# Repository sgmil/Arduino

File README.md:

# Useful Arduino templates and files
### Scripts folder contains bash scripts for accessing arduino-cli from geany
### ESPOTA.py for OTA uploads of .bin file on ESP8266
### Arduino templates/files/  contains arduino .ino and .geany files for geany

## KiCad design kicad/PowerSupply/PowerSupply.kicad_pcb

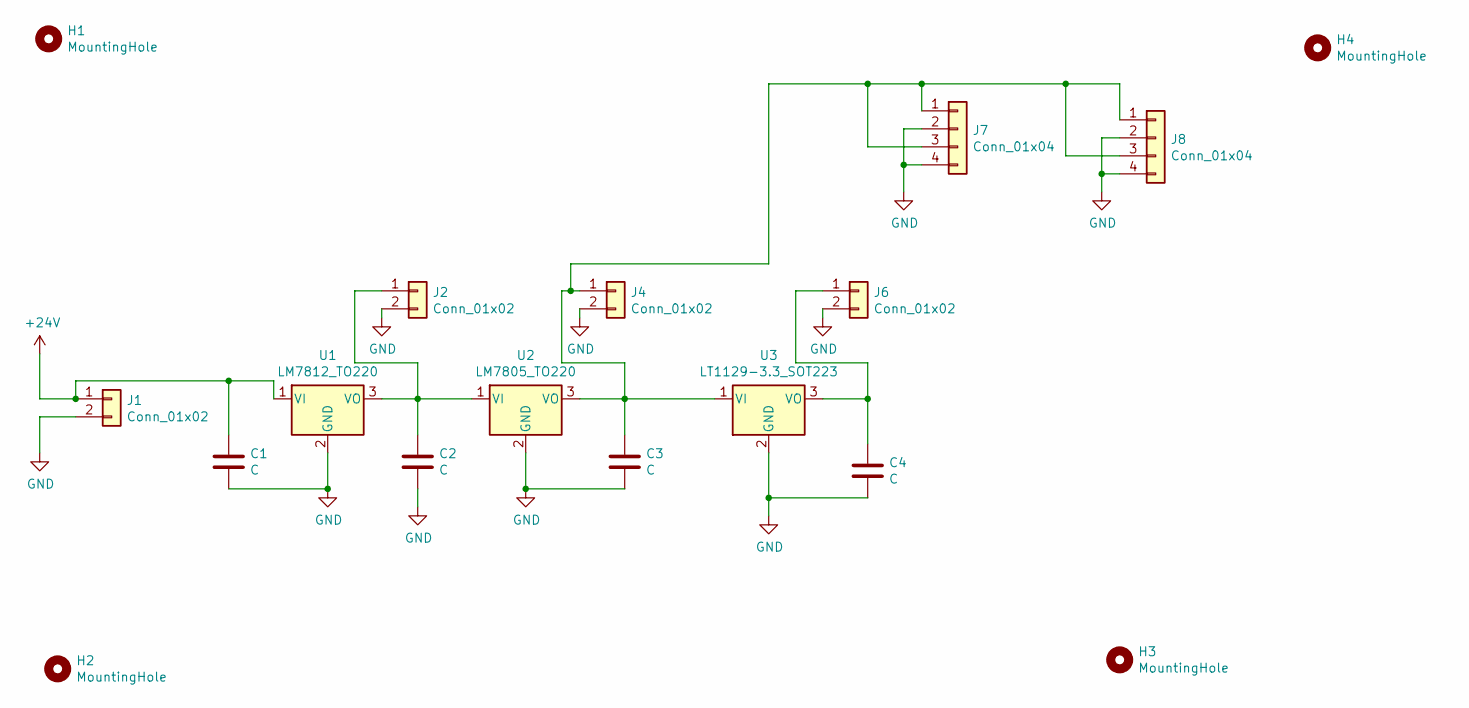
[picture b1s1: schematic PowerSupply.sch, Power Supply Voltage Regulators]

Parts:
C1, C2, C3, C4: C; CP_Radial_D5.0mm_P2.50mm
H1, H2, H3, H4: MountingHole; MountingHole_2.5mm
J1, J2, J4, J6: Conn_01x02; PINHEAD1-2
J7, J8: Conn_01x04; Pin_Header_Straight_1x04_Pitch2.54mm
U1: LM7812_TO220; TO-220-3_Vertical
U2: LM7805_TO220; TO-220-3_Vertical
U3: LT1129-3.3_SOT223; TO-220-3_Vertical

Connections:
+24V: C1.1, J1.1, U1.1 (VI)
GND: C1.2, C2.2, C3.2, C4.2, J1.2, J2.2, J4.2, J6.2, J7.2, J7.4, J8.2, J8.4, U1.2 (GND), U2.2 (GND), U3.2 (GND)
unnamed: C2.1, J2.1, U1.3 (VO), U2.1 (VI)
unnamed: C3.1, J4.1, J7.1, J7.3, J8.1, J8.3, U2.3 (VO), U3.1 (VI)
unnamed: C4.1, J6.1, U3.3 (VO)

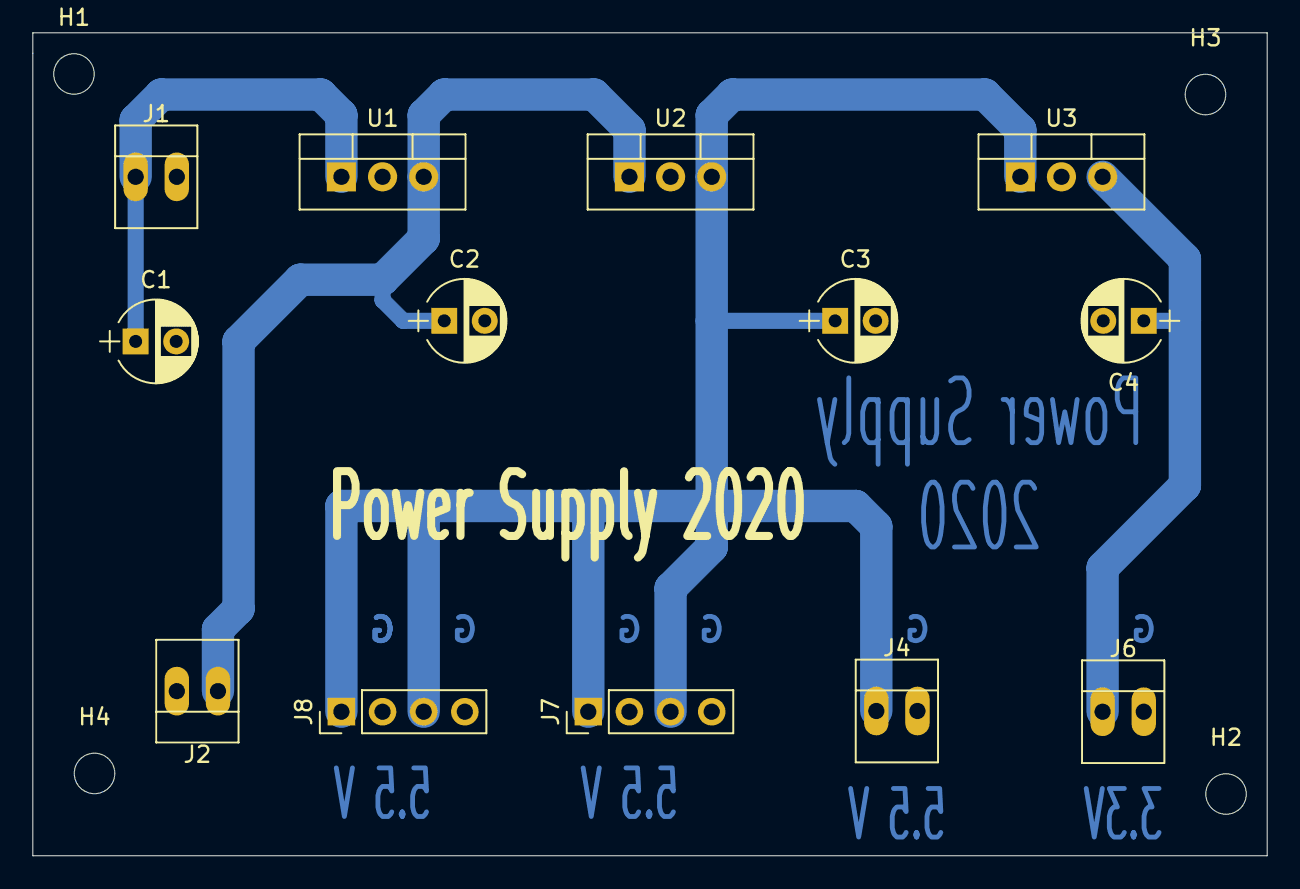
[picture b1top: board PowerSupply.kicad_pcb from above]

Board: 2 copper layers, 76.2 x 50.8 mm, 17 parts (0 on the bottom side), 5 nets.

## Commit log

2020-01-02 add extra line to top of template and adjust
2020-01-02 templates added
2020-01-03 change to sed to remove #define
2020-01-04 using #define headers
2020-01-04 modified templates for #define header
2020-01-05 header changes
2020-01-05 redo links
2020-01-05 add to setup and main
2020-01-06 clean up appearance, add documentation
2020-01-06 clean up folders
2020-01-07 added OTAok
2020-01-07 add files
2020-01-07 README
2020-01-07 add line documentation
2020-01-07 put in line documentation
2020-01-07 more documentation
2020-01-10 changed to grep
2020-01-11 cleanup
2020-01-11 tidyup
2020-01-16 added ...SensorNetwork...py as example
2020-01-17 added config files for git and bash
2020-01-19 Server captures json, updates class object
2020-01-20 Python email testing
2020-01-21 Server sending email update daily
2020-03-13 cnc'd
2020-03-18 add Power Supply kicad
2022-01-19 cleanup filesystem
2022-01-19 file cleanup
2022-01-19 ignores
2022-01-19 moves and fixes
2022-02-04 testing
